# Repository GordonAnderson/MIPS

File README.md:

# MIPS - Modular Intelligent Power System

Firmware for the MIPS controller, developed by GAA Custom Electronics, LLC. MIPS is a modular, intelligent power source platform designed specifically for mass spectrometry and ion processing applications. The firmware targets the Arduino Due (Atmel SAM3X8E, 84MHz ARM Cortex-M3) and is built using the PlatformIO ecosystem.

## Overview

MIPS provides centralized control over a collection of plug-in hardware modules through a round-robin multitasking architecture. Modules are auto-detected at startup via TWI EEPROM scanning. Each module registers itself, adds its menu entries to the system UI, and runs as an independent thread.

The system communicates with a host computer via USB (native) or serial port, with automatic detection of the active port. Ethernet and WiFi interfaces are also supported. All commands are processed through a table-driven serial command processor.

Configuration is saved to SD card (`default.cfg`) and restored automatically on startup.

## Supported Modules

| Module | Description |
|--------|-------------|
| **ARB** | Arbitrary waveform generator, up to 6 modules, with compression mode |
| **RFdriver** | RF driver for high-Q ion guides and ion traps |
| **RFamp** | RF amplifier control |
| **DCbias** | Multi-channel DC bias supply |
| **DCbiasCtrl** | DC bias control and sequencing |
| **DCbiasList** | DC bias list/table mode |
| **DCBcurrent** | DC bias current monitoring |
| **DCBswitch** | DC bias switching |
| **DAC** | SPI/CPLD-based DAC interface |
| **ADCdrv** | ADC driver |
| **FAIMS** | Field Asymmetric Ion Mobility Spectrometry driver |
| **FAIMSfb** | FAIMS feedback control |
| **HOFAIMS** | High-order FAIMS |
| **Twave** | Travelling wave ion guide driver (rev 1–5) |
| **Compressor** | Ion compression control |
| **ARBcompressor** | ARB-based compression |
| **ESI** | Electrospray ionization control |
| **Filament** | Filament/ion source control |
| **HVPS** | High voltage power supply |
| **HVPSinterface** | HVPS interface layer |
| **DIO** | Digital I/O |
| **Analog** | Analog I/O |
| **ClockGenerator** | CY22393 clock generator control |
| **FPGA** | FPGA interface |
| **FS7140** | FS7140 frequency synthesizer |
| **SC16IS740** | SC16IS740 UART bridge |
| **DMSDMSMB** | DMS/MS motherboard support |
| **ethernet** | Ethernet interface |
| **WiFi** | WiFi interface |
| **Table** | Pulse sequence table execution |
| **Log** | System logging |

## Hardware

- **Controller:** Arduino Due (Atmel SAM3X8E, 84MHz ARM Cortex-M3)
- **Display:** ILI9340 TFT with Adafruit GFX
- **Storage:** SD card (configuration and data)
- **Communication:** USB (native), UART serial, TWI (I2C), SPI, Ethernet, WiFi
- **Module bus:** TWI with board-select addressing (up to 8 modules per system)

## Build

Requires [PlatformIO](https://platformio.org/).

```bash
pio run
```

To upload:

```bash
pio run --target upload
```

All dependencies are included in the `lib/` directory. No external library paths required.

## Project Structure

```
├── src/          # Firmware source files (.cpp)
├── include/      # Project header files (.h)
├── lib/          # Local library dependencies
├── test/         # Unit tests
└── platformio.ini
```

## Author

Gordon Anderson  
GAA Custom Electronics, LLC  
gaa@owt.com

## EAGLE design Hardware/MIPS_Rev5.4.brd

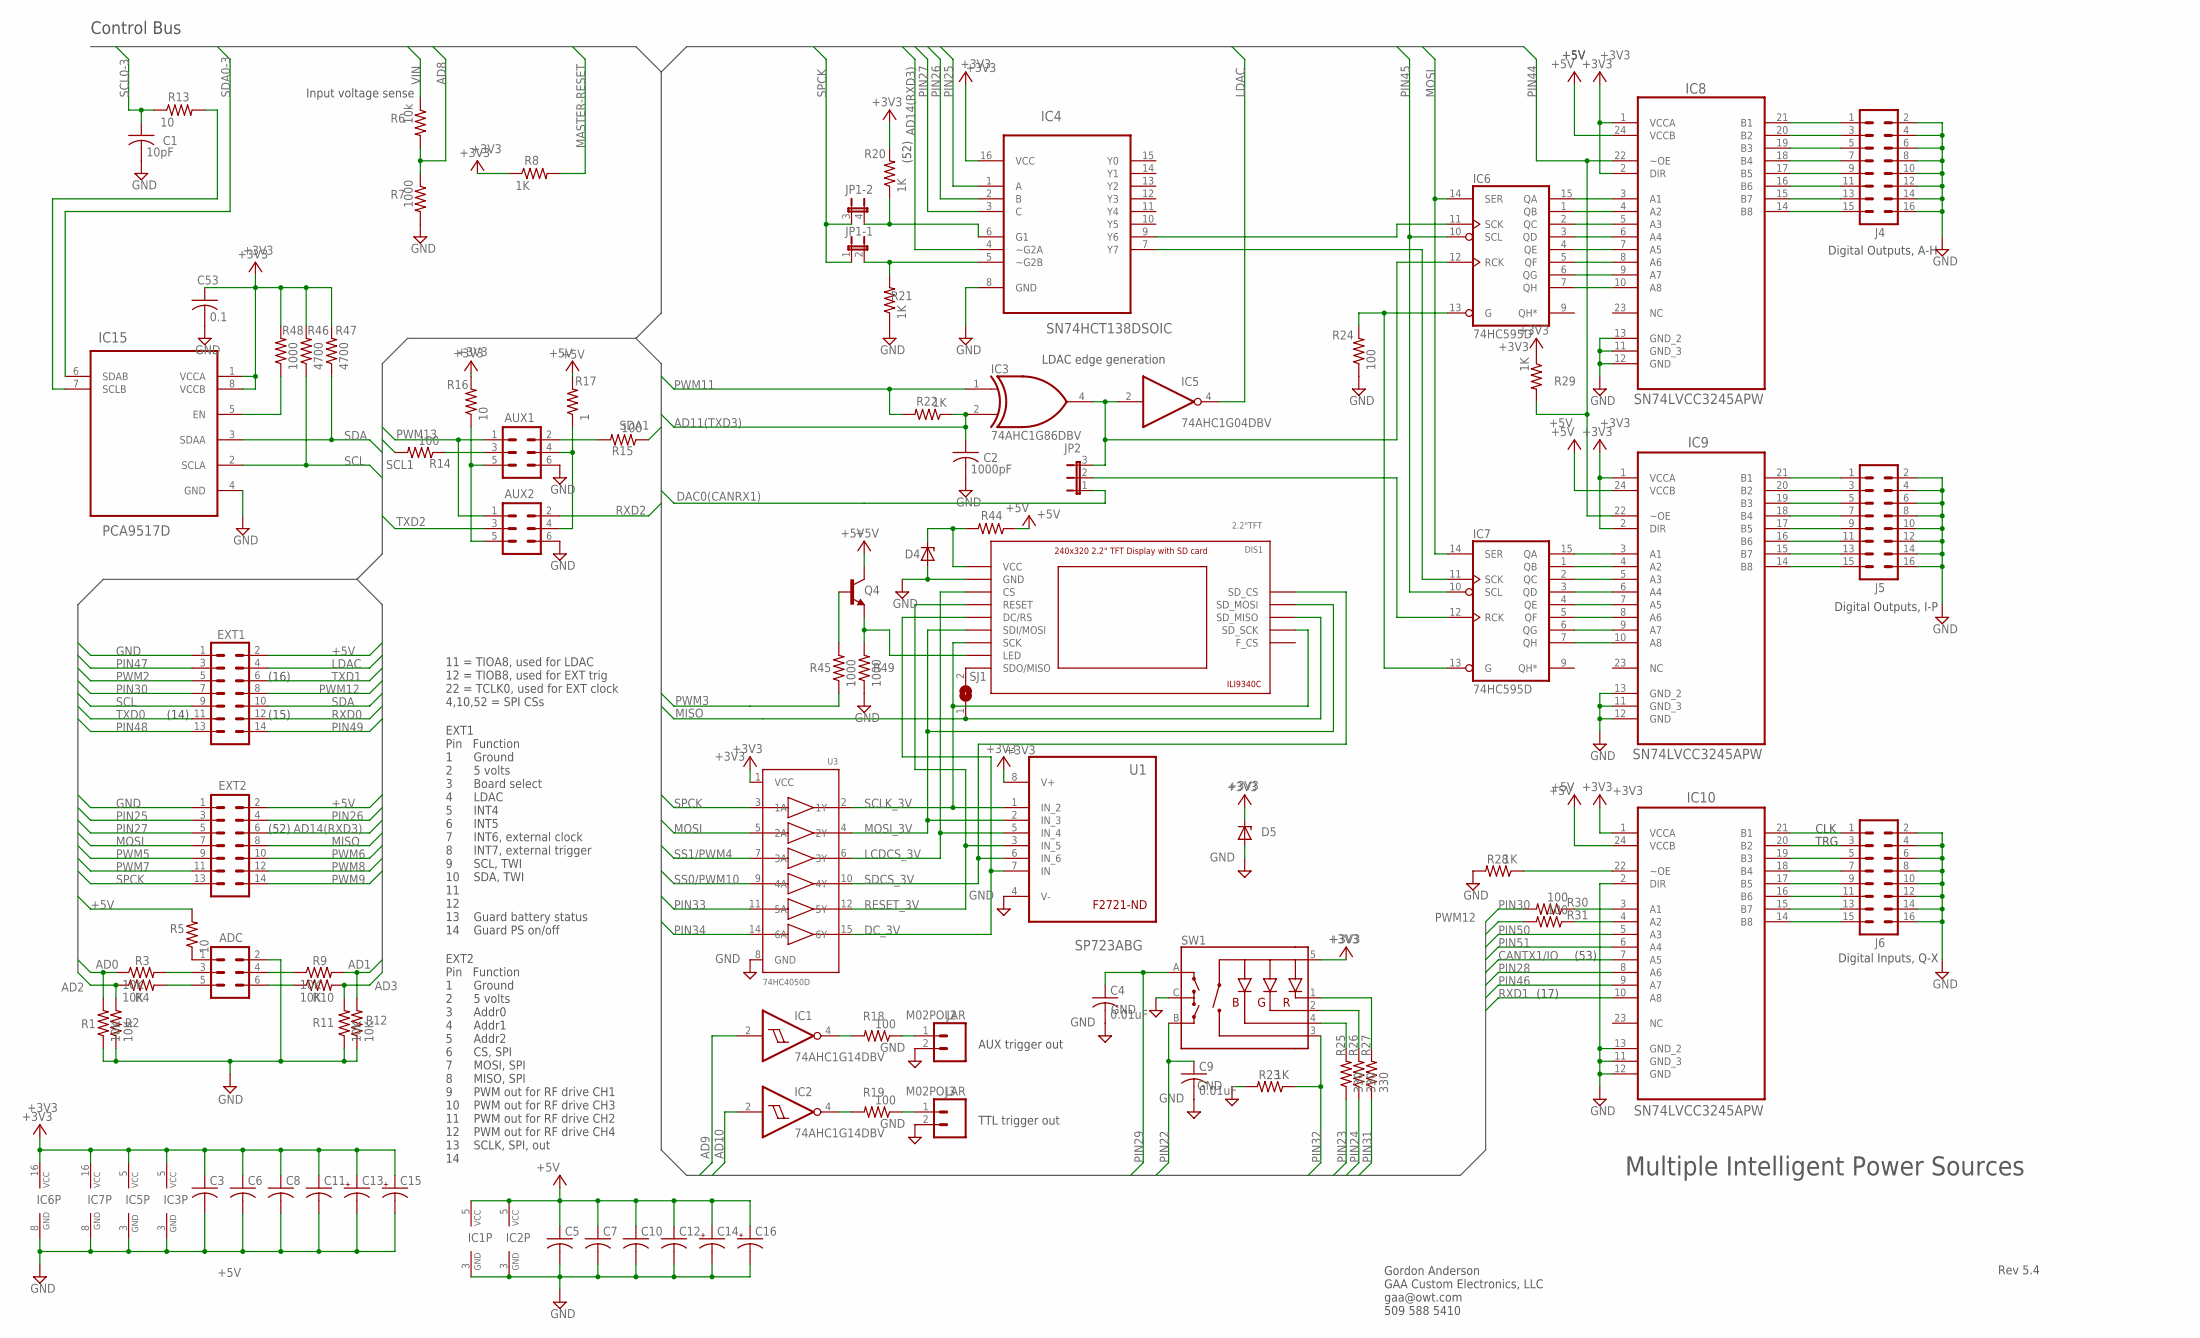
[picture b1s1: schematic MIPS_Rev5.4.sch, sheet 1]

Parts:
ADC: ML6
AUX1, AUX2: ML6
C1: 10pF; C0805
C2: 1000pF; C0805
C3, C5, C6, C7, C8, C10, C11, C12: C-USC0805; C0805
C4, C9: 0.01uF; C0805
C13, C14, C15, C16: CPOL-USA/3216-18R; A/3216-18R
C53: 0.1; C0805
D4, D5: ZENER-DIODESOD123; SOD123
DIS1: 2.2"TFT
EXT1, EXT2: ML14
IC1, IC2: 74AHC1G14DBV; SOT23-5
IC3: 74AHC1G86DBV; SOT23-5
IC4: SN74HCT138DSOIC; SO16
IC5: 74AHC1G04DBV; SOT23-5
IC6, IC7: 74HC595D; SO16
IC8, IC9, IC10: SN74LVCC3245APW; SOP65P640X120-24N
IC15: PCA9517D; SOIC127P600X175-8N
J2, J3: M02POLAR; MOLEX-1X2
J4, J5, J6: ML16
JP1: JP2QE; JP2Q
JP2: JP2E; JP2
Q4: MMBT2222ALT1-NPN-SOT23-BEC; SOT23-BEC
R1, R2, R3, R4, R9, R10, R11, R12: 10K; R0805
R5: 10; R1206
R6: 10k; R0805
R7, R45, R48, R49: 1000; R0805
R8, R20, R21, R22, R23, R28, R29: 1K; R0805
R13, R16: 10; R0805
R14, R15, R18, R19, R24, R30, R31: 100; R0805
R17: 1; R0805
R25, R26, R27: 330; R0805
R44: R-US_R0805; R0805
R46, R47: 4700; R0805
SJ1: SJ
SW1: ENCODER_RGB_CA; ENCODER_LED_3
U1: SP723ABG; SOIC127P600X175-8N
U3: 74HC4050D; SOIC16

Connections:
+3V3: C3.1, C6.1, C8.1, C11.1, C13.+, C15.+, C53.1, D5.C, IC3.5 (VCC), IC4.16 (VCC), IC5.5 (VCC), IC6.16 (VCC), IC7.16 (VCC), IC8.1 (VCCA), IC8.2 (DIR), IC9.1 (VCCA), IC9.2 (DIR), IC10.1 (VCCA), IC15.1 (VCCA), IC15.8 (VCCB), R8.1, R16.2, R20.2, R29.1, R46.2, R47.2, R48.2, SW1.5 (+), U1.8 (V+), U3.1 (VCC); also elsewhere on the board
+5V: C5.1, C7.1, C10.1, C12.1, C14.+, C16.+, EXT1.2, EXT2.2, IC1.5 (VCC), IC2.5 (VCC), IC8.24 (VCCB), IC9.24 (VCCB), IC10.24 (VCCB), Q4.C, R5.2, R17.2, R44.1; also elsewhere on the board
AD0: R1.2, R3.1; also elsewhere on the board
AD1: R9.2, R12.2; also elsewhere on the board
AD2: R2.2, R4.1; also elsewhere on the board
AD3: R10.2, R11.2; also elsewhere on the board
AD8: R6.2, R7.1; also elsewhere on the board
AD9: IC1.2 (I); also elsewhere on the board
AD10: IC2.2 (I); also elsewhere on the board
AD11(TXD3): C2.1, IC3.2 (I1), R22.1; also elsewhere on the board
AD14(RXD3): EXT2.6, IC4.4 (~G2A); also elsewhere on the board
CANTX1/IO: IC10.7 (A5); also elsewhere on the board
DAC0(CANRX1): JP2.1; also elsewhere on the board
DC_3V: DIS1.DC/RS, U1.7 (IN), U3.15 (6Y)
GND: ADC.2, AUX1.6, AUX2.6, C1.2, C2.2, C3.2, C4.2, C5.2, C6.2, C7.2, C8.2, C9.2, C10.2, C11.2, C12.2, C13.-, C14.-, C15.-, C16.-, C53.2, D4.A, D5.A, DIS1.GND, EXT1.1, EXT2.1, IC1.3 (GND), IC2.3 (GND), IC3.3 (GND), IC4.8 (GND), IC5.3 (GND), IC6.8 (GND), IC7.8 (GND), IC8.11 (GND_3), IC8.12 (GND), IC8.13 (GND_2), IC9.11 (GND_3), IC9.12 (GND), IC9.13 (GND_2), IC10.2 (DIR), IC10.11 (GND_3), IC10.12 (GND), IC10.13 (GND_2), IC15.4 (GND), J2.2, J3.2, J4.2, J4.4, J4.6, J4.8, J4.10, J4.12, J4.14, J4.16, J5.2, J5.4, J5.6, J5.8, J5.10, J5.12, J5.14, J5.16, J6.2, J6.4, J6.6, J6.8, J6.10, J6.12, J6.14, J6.16, R1.1, R2.1, R7.2, R11.1, R12.1, R21.1, R23.2, R24.1, R28.2, R49.1, SW1.C, U1.4 (V-), U3.8 (GND); also elsewhere on the board
LCDCS_3V: DIS1.CS, U1.5 (IN_4), U3.6 (3Y)
LDAC: EXT1.4, IC5.4 (O)
MASTER-RESET: R8.2; also elsewhere on the board
MISO: DIS1.SD_MISO, EXT2.8, SJ1.1; also elsewhere on the board
MOSI: EXT2.7, IC6.14 (SER), IC7.14 (SER), U3.5 (2A); also elsewhere on the board
MOSI_3V: DIS1.SDI/MOSI, DIS1.SD_MOSI, U1.2 (IN_3), U3.4 (2Y)
unnamed: IC6.15 (QA), IC8.3 (A1)
unnamed: IC6.1 (QB), IC8.4 (A2)
unnamed: IC6.2 (QC), IC8.5 (A3)
unnamed: IC6.3 (QD), IC8.6 (A4)
unnamed: IC6.4 (QE), IC8.7 (A5)
unnamed: IC6.5 (QF), IC8.8 (A6)
unnamed: IC6.6 (QG), IC8.9 (A7)
unnamed: IC6.7 (QH), IC8.10 (A8)
unnamed: IC7.1 (QB), IC9.4 (A2)
unnamed: IC7.2 (QC), IC9.5 (A3)
unnamed: IC7.3 (QD), IC9.6 (A4)
unnamed: IC7.4 (QE), IC9.7 (A5)
unnamed: IC7.5 (QF), IC9.8 (A6)
unnamed: IC7.6 (QG), IC9.9 (A7)
unnamed: IC7.7 (QH), IC9.10 (A8)
unnamed: IC7.15 (QA), IC9.3 (A1)
unnamed: IC9.21 (B1), J5.1
unnamed: IC9.20 (B2), J5.3
unnamed: IC9.19 (B3), J5.5
unnamed: IC9.18 (B4), J5.7
unnamed: IC9.17 (B5), J5.9
unnamed: IC9.16 (B6), J5.11
unnamed: IC9.15 (B7), J5.13
unnamed: IC9.14 (B8), J5.15
unnamed: IC8.21 (B1), J4.1
unnamed: IC8.20 (B2), J4.3
unnamed: IC8.19 (B3), J4.5
unnamed: IC8.18 (B4), J4.7
unnamed: IC8.17 (B5), J4.9
unnamed: IC8.16 (B6), J4.11
unnamed: IC8.15 (B7), J4.13
unnamed: IC8.14 (B8), J4.15
unnamed: IC10.21 (B1), J6.1
unnamed: IC10.20 (B2), J6.3
unnamed: IC10.19 (B3), J6.5
unnamed: IC10.18 (B4), J6.7
unnamed: IC10.17 (B5), J6.9
unnamed: IC10.16 (B6), J6.11
unnamed: IC10.15 (B7), J6.13
unnamed: IC10.14 (B8), J6.15
unnamed: IC4.7 (Y7), IC7.11 (SCK)
unnamed: ADC.3, R3.2
unnamed: ADC.1, R5.1
unnamed: ADC.4, R9.1
unnamed: ADC.5, R4.2
unnamed: IC10.22 (~OE), R28.1
unnamed: ADC.6, R10.1
unnamed: IC7.12 (RCK), JP2.2
unnamed: IC15.5 (EN), R48.1
unnamed: IC10.3 (A1), R30.1
unnamed: IC10.4 (A2), R31.1
unnamed: D4.C, DIS1.P$9VCC (VCC), R44.2
unnamed: IC15.7 (SCLB), R13.2
unnamed: DIS1.SDO/MISO, SJ1.2
unnamed: IC2.4 (O), R19.2
unnamed: IC1.4 (O), R18.2
unnamed: J3.1, R19.1
unnamed: IC6.13 (G), IC7.13 (G), R24.2
unnamed: J2.1, R18.1
unnamed: AUX1.2, R15.2
unnamed: AUX1.3, R14.1
unnamed: AUX1.4, AUX2.4, R17.1
unnamed: AUX1.5, AUX2.5, R16.1
unnamed: DIS1.LED, Q4.E, R49.2
unnamed: Q4.B, R45.2
unnamed: IC4.9 (Y6), IC6.11 (SCK)
unnamed: IC4.5 (~G2B), JP1.2, R21.2
unnamed: IC4.6 (G1), JP1.4 (2), R20.1
unnamed: R27.2, SW1.1 (-R)
unnamed: R26.2, SW1.2 (-G)
unnamed: R25.2, SW1.4 (-B)
PIN22: C9.1, SW1.B; also elsewhere on the board
PIN23: R25.1; also elsewhere on the board
PIN24: R26.1; also elsewhere on the board
PIN25: EXT2.3, IC4.1 (A); also elsewhere on the board
PIN26: EXT2.4, IC4.2 (B); also elsewhere on the board
PIN27: EXT2.5, IC4.3 (C); also elsewhere on the board
PIN28: IC10.8 (A6); also elsewhere on the board
PIN29: C4.1, SW1.A; also elsewhere on the board
PIN30: EXT1.7, R30.2; also elsewhere on the board
PIN31: R27.1; also elsewhere on the board
PIN32: R23.1, SW1.3 (SW); also elsewhere on the board
PIN33: U3.11 (5A); also elsewhere on the board
PIN34: U3.14 (6A); also elsewhere on the board
PIN44: IC8.22 (~OE), IC9.22 (~OE), R29.2; also elsewhere on the board
PIN45: IC6.10 (SCL), IC7.10 (SCL); also elsewhere on the board
PIN46: IC10.9 (A7); also elsewhere on the board
PIN47: EXT1.3; also elsewhere on the board
PIN48: EXT1.13; also elsewhere on the board
PIN49: EXT1.14; also elsewhere on the board
PIN50: IC10.5 (A3); also elsewhere on the board
PIN51: IC10.6 (A4); also elsewhere on the board
PWM2: EXT1.5; also elsewhere on the board
PWM3: R45.1; also elsewhere on the board
PWM5: EXT2.9; also elsewhere on the board
PWM6: EXT2.10; also elsewhere on the board
PWM7: EXT2.11; also elsewhere on the board
PWM8: EXT2.12; also elsewhere on the board
PWM9: EXT2.14; also elsewhere on the board
PWM11: IC3.1 (I0), R22.2; also elsewhere on the board
PWM12: EXT1.8, R31.2; also elsewhere on the board
PWM13: AUX1.1, AUX2.1; also elsewhere on the board
RESET_3V: DIS1.RESET, U1.3 (IN_5), U3.12 (5Y)
RXD0: EXT1.12; also elsewhere on the board
RXD1: IC10.10 (A8); also elsewhere on the board
RXD2: AUX2.2; also elsewhere on the board
SCL: EXT1.9, IC15.2 (SCLA), R46.1
SCL0-3: C1.1, R13.1; also elsewhere on the board
SCL1: R14.2; also elsewhere on the board
SCLK_3V: DIS1.SCK, DIS1.SD_SCK, U1.1 (IN_2), U3.2 (1Y)
SDA: EXT1.10, IC15.3 (SDAA), R47.1
SDA0-3: IC15.6 (SDAB); also elsewhere on the board
SDA1: R15.1; also elsewhere on the board
SDCS_3V: DIS1.SD_CS, U1.6 (IN_6), U3.10 (4Y)
SPCK: EXT2.13, JP1.1, JP1.3 (1), U3.3 (1A); also elsewhere on the board
SS0/PWM10: U3.9 (4A); also elsewhere on the board
SS1/PWM4: U3.7 (3A); also elsewhere on the board
TXD0: EXT1.11; also elsewhere on the board
TXD1: EXT1.6; also elsewhere on the board
TXD2: AUX2.3; also elsewhere on the board
VIN: R6.1; also elsewhere on the board
~LDAC: IC3.4 (O), IC5.2 (I), IC6.12 (RCK), JP2.3

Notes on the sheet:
EXT1 Pin Function 1 Ground 2 5 volts 3 Board select 4 LDAC 5 INT4 6 INT5 7 INT6, external clock 8 INT7, external trigger 9 SCL, TWI 10 SDA, TWI 11 12 13 Guard battery status 14 Guard PS on/off
EXT2 Pin Function 1 Ground 2 5 volts 3 Addr0 4 Addr1 5 Addr2 6 CS, SPI 7 MOSI, SPI 8 MISO, SPI 9 PWM out for RF drive CH1 10 PWM out for RF drive CH3 11 PWM out for RF drive CH2 12 PWM out for RF drive CH4 13 SCLK, SPI, out 14
11 = TIOA8, used for LDAC 12 = TIOB8, used for EXT trig 22 = TCLK0, used for EXT clock 4,10,52 = SPI CSs
Gordon Anderson GAA Custom Electronics, LLC gaa@owt.com 509 588 5410
Multiple Intelligent Power Sources
Digital Outputs, A-H
Digital Outputs, I-P
Digital Inputs, Q-X
CLK
TRG
Rev 5.4
TTL trigger out
LDAC edge generation
AUX trigger out
(17)
(53)
(52)
(14)
(16)
(15)
Input voltage sense
Control Bus
F2721-ND

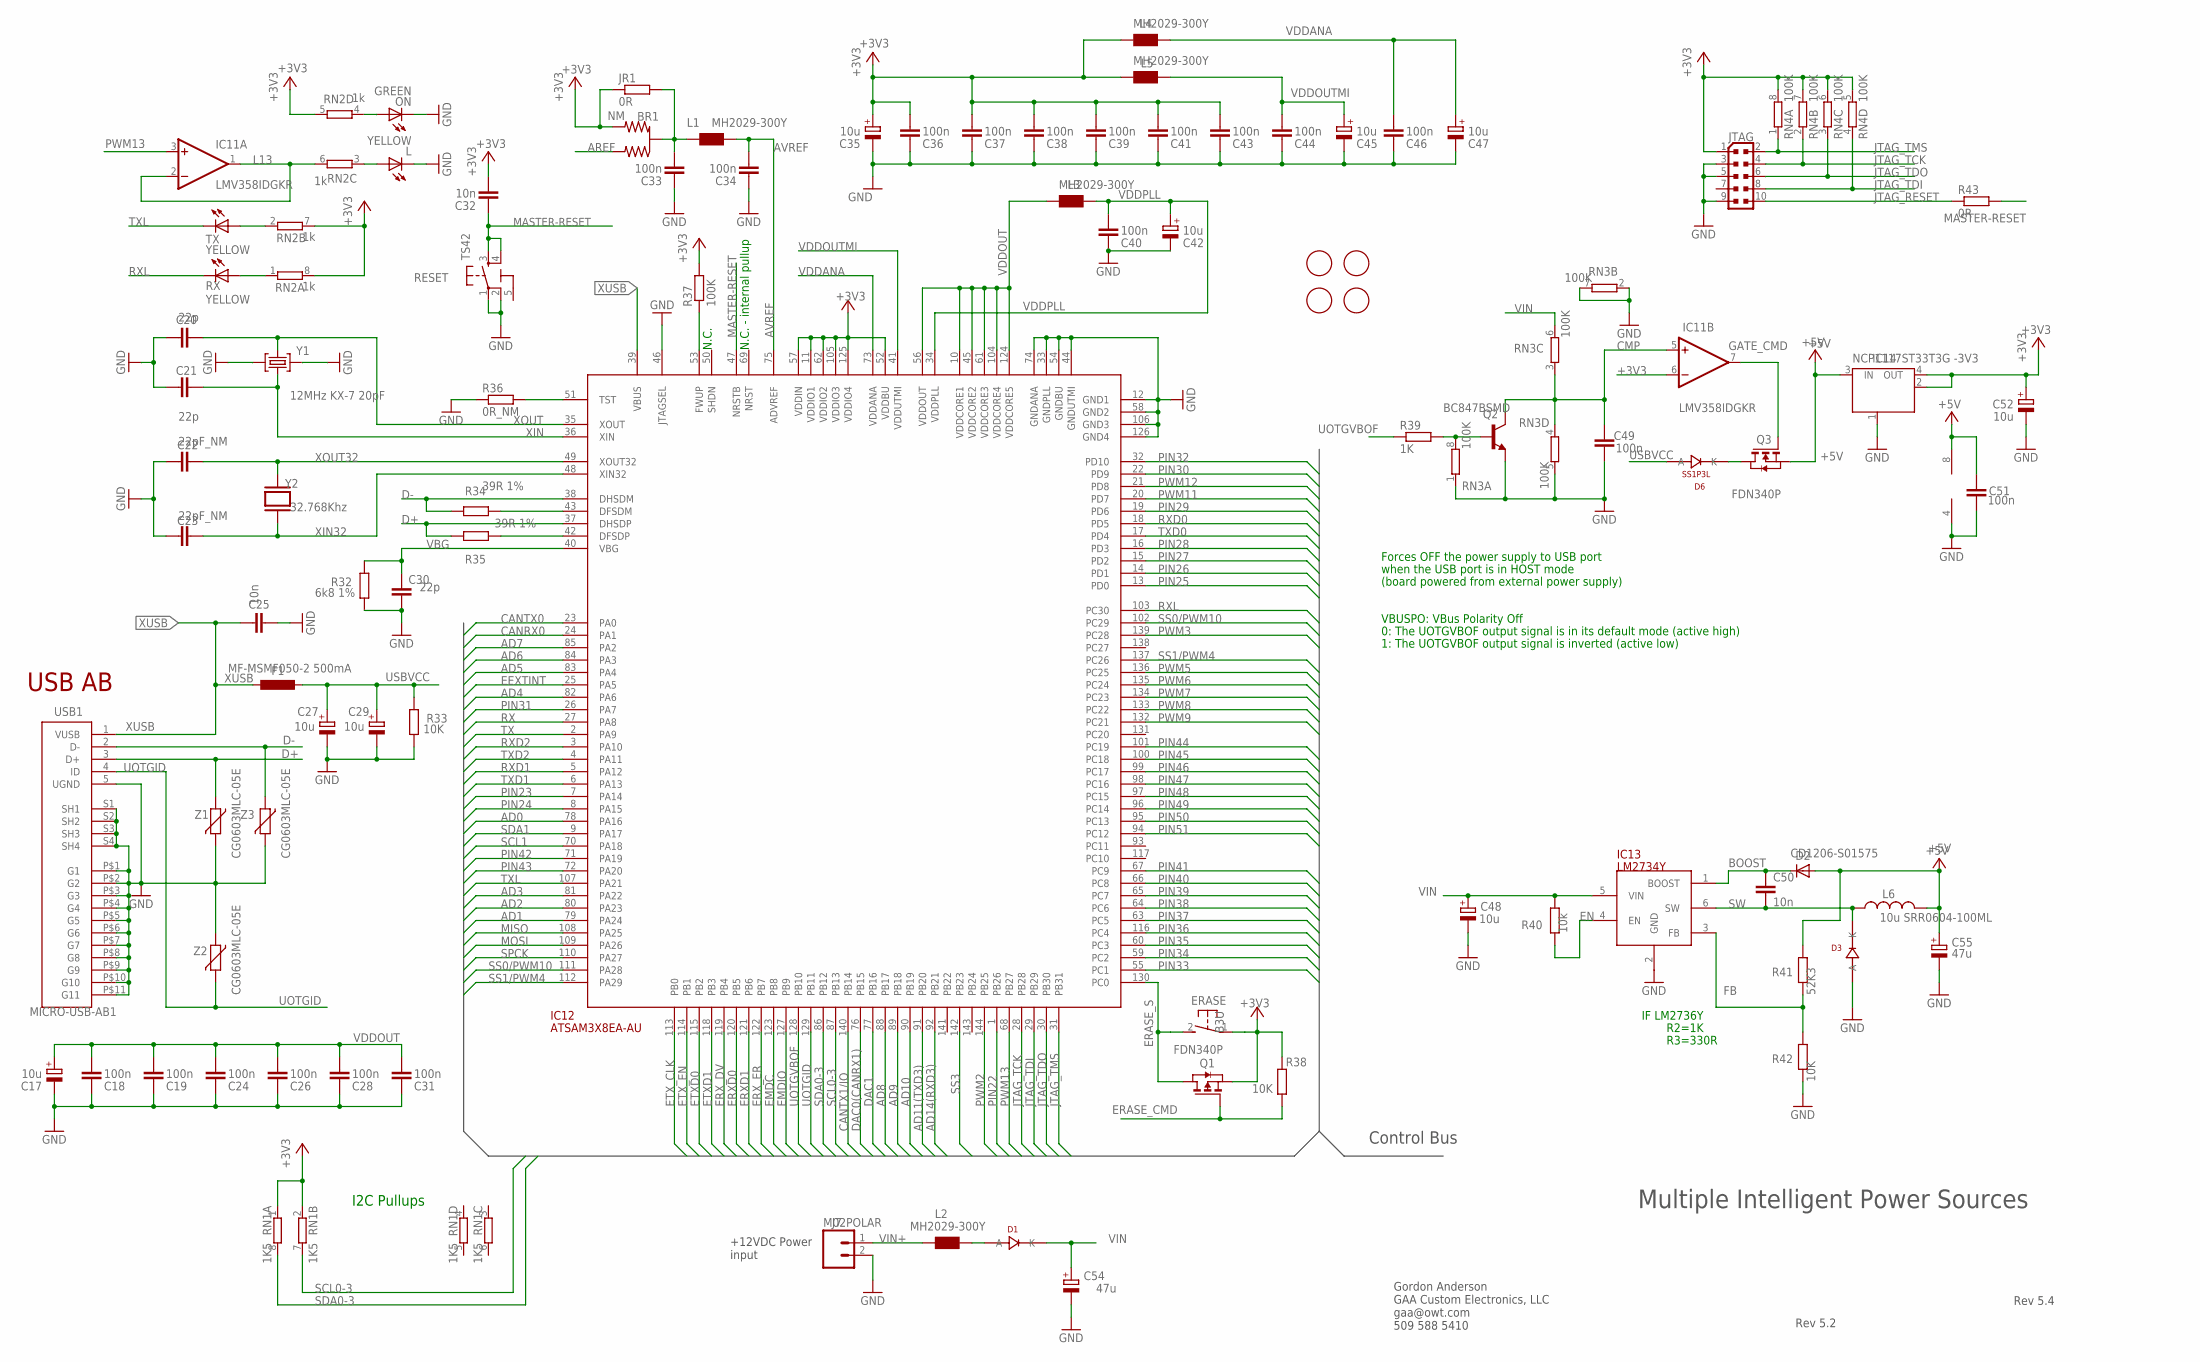
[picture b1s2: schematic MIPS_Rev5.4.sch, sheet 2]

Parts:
BR1: NM; J0402
C17, C27, C29, C35, C42, C45, C47, C48, C52: 10u; SMC_B
C18, C19, C24, C26, C28, C31, C33, C34, C36, C37, C38, C39, C40, C41, C43, C44, C46, C49, C51: 100n; C0402
C20, C21, C30: 22p; C0402
C22, C23: 22pF_NM; C0402
C25, C32: 10n; C0402
C50: 10n; C0603-ROUND
C54, C55: 47u; PANASONIC_D
D1, D3, D6: SS1P3L; DO220AAL
D2: CD1206-S01575; MINIMELF
ERASE: B3U
F1: MF-MSMF050-2 500mA; L1812
FID1, FID2, FID3, FID4: FIDUCIALMOUNT; FIDUCIA-MOUNT
IC11: LMV358IDGKR; MSOP08
IC12: ATSAM3X8EA-AU; LQFP144
IC13: LM2734Y; SOT23-6
IC14: NCP1117ST33T3G -3V3; SOT223
J7: M02POLAR; MOLEX-1X2
JR1: 0R; R0402
JTAG: PINHEAD_PINHD-2X5PASSO127; PINHEAD_2X05_127
L: YELLOW; CHIP-LED0805
L1, L2, L3, L4, L5: MH2029-300Y; 0805
L6: 10u SRR0604-100ML; SRR0604
ON: GREEN; CHIP-LED0805
Q1, Q3: FDN340P; SOT-23
Q2: BC847BSMD; SOT23
R32: 6k8 1%; R0603-ROUND
R33, R38: 10K; R0402
R34, R35: 39R 1%; R0402
R36: 0R_NM; R0402
R37: 100K; R0402
R39: 1K; R0402
R40: 10k; R0402
R41: 52K3; R0603-ROUND
R42: 10K; R0603-ROUND
R43: 0R; R0402
RESET: TS42
RN1: 1K5; CAT16
RN2: 1k; CAY16
RN3, RN4: 100K; CAT16
RX: YELLOW; CHIP-LED0805
TX: YELLOW; CHIP-LED0805
USB1: MICRO-USB-AB1; MCR-AB1-S-RA-SMT
Y1: 12MHz KX-7 20pF; CRYSTAL-3.2-2.5
Y2: 32.768Khz; XTAL_CM8V-T1A-32.768KHZ-9PF-20PPM-TA-QC
Z1, Z2, Z3: CG0603MLC-05E; CT/CN0603

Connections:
5-GND: RESET.5 (5-GND)
+3V3: BR1.3 (2), C32.2, C35.+, C36.2, C37.2, C38.2, C39.2, C41.2, C43.2, C52.+, ERASE.1, IC11.6 (-IN), IC12.11 (VDDIO1), IC12.52 (VDDBU), IC12.57 (VDDIN), IC12.62 (VDDIO2), IC12.105 (VDDIO3), IC12.125 (VDDIO4), IC14.2 (OUT), IC14.4 (OUT), JR1.1, JTAG.1, L4.1, L5.1, Q1.2 (S), R37.2, R38.2, RN1.1, RN1.2 (1), RN2.5 (2), RN2.7 (2), RN2.8 (2), RN4.5 (2), RN4.6 (2), RN4.7 (2), RN4.8 (2); also elsewhere on the board
+5V: C51.2, C55.+, D2.A, IC11.8 (V+), IC14.3 (IN), L6.P$2 (2), Q3.2 (S), R41.1; also elsewhere on the board
AD0: IC12.78 (PA16); also elsewhere on the board
AD1: IC12.79 (PA24); also elsewhere on the board
AD2: IC12.80 (PA23); also elsewhere on the board
AD3: IC12.81 (PA22); also elsewhere on the board
AD4: IC12.82 (PA6)
AD5: IC12.83 (PA4)
AD6: IC12.84 (PA3)
AD7: IC12.85 (PA2)
AD8: IC12.88 (PB17); also elsewhere on the board
AD9: IC12.89 (PB18); also elsewhere on the board
AD10: IC12.90 (PB19); also elsewhere on the board
AD11(TXD3): IC12.91 (PB20); also elsewhere on the board
AD14(RXD3): IC12.92 (PB21); also elsewhere on the board
AREF: BR1.1
AVREF: C34.2, IC12.75 (ADVREF), L1.2
AVREFL: BR1.2 (C), C33.2, JR1.2, L1.1
BOOST: C50.1, D2.C, IC13.1 (BOOST)
CANRX0: IC12.24 (PA1)
CANTX0: IC12.23 (PA0)
CANTX1/IO: IC12.140 (PB14); also elsewhere on the board
CMP: C49.2, IC11.5 (+IN), Q2.3 (C), RN3.3 (1), RN3.4 (1)
D+: IC12.37 (DHSDP), R35.1, USB1.3 (D+), Z1.1
D-: IC12.38 (DHSDM), R34.1, USB1.2 (D-), Z3.1
DAC0(CANRX1): IC12.76 (PB15); also elsewhere on the board
DAC1: IC12.77 (PB16)
EEXTINT: IC12.25 (PA5)
EMDC: IC12.123 (PB8)
EMDIO: IC12.127 (PB9)
EN: IC13.4 (EN), R40.2
ERASE_CMD: Q1.3 (G), R38.1
ERASE_S: ERASE.2, IC12.130 (PC0), Q1.1 (D)
ERXD0: IC12.120 (PB5)
ERXD1: IC12.121 (PB6)
ERX_DV: IC12.119 (PB4)
ERX_ER: IC12.122 (PB7)
ETXD0: IC12.115 (PB2)
ETXD1: IC12.118 (PB3)
ETX_CLK: IC12.113 (PB0)
ETX_EN: IC12.114 (PB1)
FB: IC13.3 (FB), R41.2, R42.1
GATE_CMD: IC11.7 (OUT), Q3.3 (G)
GND: C17.-, C18.1, C19.1, C20.2, C21.2, C22.2, C23.2, C24.1, C25.2, C26.1, C27.-, C28.1, C29.-, C30.2, C31.1, C33.1, C34.1, C35.-, C36.1, C37.1, C38.1, C39.1, C40.1, C41.1, C42.-, C43.1, C44.1, C45.-, C46.1, C47.-, C48.-, C49.1, C51.1, C52.-, C54.-, C55.-, D3.P$2 (A), IC11.4 (V-), IC12.12 (GND1), IC12.33 (GNDPLL), IC12.44 (GNDUTMI), IC12.46 (JTAGSEL), IC12.54 (GNDBU), IC12.58 (GND2), IC12.74 (GNDANA), IC12.106 (GND3), IC12.126 (GND4), IC13.2 (GND), IC14.1 (GND/ADJ), J7.2, JTAG.3, JTAG.5, JTAG.9, L.C, ON.C, Q2.2 (E), R32.1, R33.1, R36.1, R42.2, RESET.1, RESET.2, RN3.1, RN3.2 (1), RN3.5 (2), RN3.7 (2), USB1.5 (UGND), USB1.P$1 (G1), USB1.P$2 (G2), USB1.P$3 (G3), USB1.P$4 (G4), USB1.P$5 (G5), USB1.P$6 (G6), USB1.P$7 (G7), USB1.P$8 (G8), USB1.P$9 (G9), USB1.P$10 (G10), USB1.P$11 (G11), USB1.S1 (SH1), USB1.S2 (SH2), USB1.S3 (SH3), USB1.S4 (SH4), Y1.2 (GND), Y1.4 (GND), Z1.2, Z2.1, Z3.2; also elsewhere on the board
JTAG_RESET: JTAG.10, R43.1
JTAG_TCK: IC12.28 (PB28), JTAG.4, RN4.2 (1)
JTAG_TDI: IC12.29 (PB29), JTAG.8, RN4.4 (1)
JTAG_TDO: IC12.30 (PB30), JTAG.6, RN4.3 (1)
JTAG_TMS: IC12.31 (PB31), JTAG.2, RN4.1
L13: IC11.1 (OUT), IC11.2 (-IN), RN2.6 (2)
MASTER-RESET: C32.1, IC12.47 (NRSTB), R43.2, RESET.3, RESET.4; also elsewhere on the board
MISO: IC12.108 (PA25); also elsewhere on the board
MOSI: IC12.109 (PA26); also elsewhere on the board
unnamed: ON.A, RN2.4 (1)
unnamed: RN2.1, RX.A
unnamed: RN2.2 (1), TX.A
unnamed: L.A, RN2.3 (1)
unnamed: IC12.43 (DFSDM), R34.2
unnamed: IC12.42 (DFSDP), R35.2
unnamed: IC12.51 (TST), R36.2
unnamed: Q2.1 (B), R39.2, RN3.8 (2)
unnamed: IC12.53 (FWUP), R37.1
unnamed: D6.P$1 (K), Q3.1 (D)
unnamed: D1.P$2 (A), L2.1
PIN22: IC12.1 (PB26); also elsewhere on the board
PIN23: IC12.7 (PA14); also elsewhere on the board
PIN24: IC12.8 (PA15); also elsewhere on the board
PIN25: IC12.13 (PD0); also elsewhere on the board
PIN26: IC12.14 (PD1); also elsewhere on the board
PIN27: IC12.15 (PD2); also elsewhere on the board
PIN28: IC12.16 (PD3); also elsewhere on the board
PIN29: IC12.19 (PD6); also elsewhere on the board
PIN30: IC12.22 (PD9); also elsewhere on the board
PIN31: IC12.26 (PA7); also elsewhere on the board
PIN32: IC12.32 (PD10); also elsewhere on the board
PIN33: IC12.55 (PC1); also elsewhere on the board
PIN34: IC12.59 (PC2); also elsewhere on the board
PIN35: IC12.60 (PC3)
PIN36: IC12.116 (PC4)
PIN37: IC12.63 (PC5)
PIN38: IC12.64 (PC6)
PIN39: IC12.65 (PC7)
PIN40: IC12.66 (PC8)
PIN41: IC12.67 (PC9)
PIN42: IC12.71 (PA19)
PIN43: IC12.72 (PA20)
PIN44: IC12.101 (PC19); also elsewhere on the board
PIN45: IC12.100 (PC18); also elsewhere on the board
PIN46: IC12.99 (PC17); also elsewhere on the board
PIN47: IC12.98 (PC16); also elsewhere on the board
PIN48: IC12.97 (PC15); also elsewhere on the board
PIN49: IC12.96 (PC14); also elsewhere on the board
PIN50: IC12.95 (PC13); also elsewhere on the board
PIN51: IC12.94 (PC12); also elsewhere on the board
PWM2: IC12.144 (PB25); also elsewhere on the board
PWM3: IC12.139 (PC28); also elsewhere on the board
PWM5: IC12.136 (PC25); also elsewhere on the board
PWM6: IC12.135 (PC24); also elsewhere on the board
PWM7: IC12.134 (PC23); also elsewhere on the board
PWM8: IC12.133 (PC22); also elsewhere on the board
PWM9: IC12.132 (PC21); also elsewhere on the board
PWM11: IC12.20 (PD7); also elsewhere on the board
PWM12: IC12.21 (PD8); also elsewhere on the board
PWM13: IC11.3 (+IN), IC12.68 (PB27); also elsewhere on the board
RX: IC12.27 (PA8)
RXD0: IC12.18 (PD5); also elsewhere on the board
RXD1: IC12.5 (PA12); also elsewhere on the board
RXD2: IC12.3 (PA10); also elsewhere on the board
RXL: IC12.103 (PC30), RX.C
SCL0-3: IC12.87 (PB13), RN1.7 (2); also elsewhere on the board
SCL1: IC12.70 (PA18); also elsewhere on the board
SDA0-3: IC12.86 (PB12), RN1.8 (2); also elsewhere on the board
SDA1: IC12.9 (PA17); also elsewhere on the board
SPCK: IC12.110 (PA27); also elsewhere on the board
SS0/PWM10: IC12.102 (PC29), IC12.111 (PA28); also elsewhere on the board
SS1/PWM4: IC12.112 (PA29), IC12.137 (PC26); also elsewhere on the board
SS3: IC12.142 (PB23)
SW: C50.2, D3.P$1 (K), IC13.6 (SW), L6.P$1 (1)
TX: IC12.2 (PA9)
TXD0: IC12.17 (PD4); also elsewhere on the board
TXD1: IC12.6 (PA13); also elsewhere on the board
TXD2: IC12.4 (PA11); also elsewhere on the board
TXL: IC12.107 (PA21), TX.C
UOTGID: IC12.129 (PB11), USB1.4 (ID), Z2.2
UOTGVBOF: IC12.128 (PB10), R39.1
USBVCC: C27.+, C29.+, D6.P$2 (A), F1.1, R33.2
VBG: C30.1, IC12.40 (VBG), R32.2
VDDANA: C46.2, C47.+, IC12.73 (VDDANA), L4.2
VDDOUT: C17.+, C18.2, C19.2, C24.2, C26.2, C28.2, C31.2, IC12.10 (VDDCORE1), IC12.45 (VDDCORE2), IC12.56 (VDDOUT), IC12.61 (VDDCORE3), IC12.104 (VDDCORE4), IC12.124 (VDDCORE5), L3.1
VDDOUTMI: C44.2, C45.+, IC12.41 (VDDUTMI), L5.2
VDDPLL: C40.2, C42.+, IC12.34 (VDDPLL), L3.2
VIN: C48.+, C54.+, D1.P$1 (K), IC13.5 (VIN), R40.1, RN3.6 (2); also elsewhere on the board
VIN+: J7.1, L2.2
XIN: C21.1, IC12.36 (XIN), Y1.1 (C1)
XIN32: C23.1, IC12.48 (XIN32), Y2.2
XOUT: C20.1, IC12.35 (XOUT), Y1.3 (C2)
XOUT32: C22.1, IC12.49 (XOUT32), Y2.1
XUSB: C25.1, F1.2, IC12.39 (VBUS), USB1.1 (VUSB)

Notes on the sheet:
USB AB
Forces OFF the power supply to USB port
when the USB port is in HOST mode
(board powered from external power supply)
N.C.
VBUSPO: VBus Polarity Off
0: The UOTGVBOF output signal is in its default mode (active high)
1: The UOTGVBOF output signal is inverted (active low)
I2C Pullups
IF LM2736Y
R2=1K
R3=330R
N.C. - internal pullup
+12VDC Power input
Control Bus
Rev 5.4
Gordon Anderson GAA Custom Electronics, LLC gaa@owt.com 509 588 5410
Multiple Intelligent Power Sources
Rev 5.2

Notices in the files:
parts and their libraries:
SparkFun-Electromechanical: Licensing: Creative Commons ShareAlike 4.0 International - https://creativecommons.org/licenses/by-sa/4.0
